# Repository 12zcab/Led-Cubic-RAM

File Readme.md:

# A SOUP-A COOL RAM-based LED CUBE for Retro Computers!
## Images

## Zine Page

## What it does?
It have a normal SRAM pinout for Retro Computer. HOWEVER,ANY DATA YOU STORED INTO IT WILL BE RESULTED AS LIGHT SHINING!!!!
Each RGB LED = 1 Byte from 0 to FF , meaning it have 16 Color Depth for each channel (RGB)
It's works similar to a VRAM with a parallel Dual-DataBus CMOS SRAM.
Really Cool for retro computers as a Screen or a Output or even for Debugging
## Why I made this?
Because I have designed and will design many Z80 and 8086,88 based retro computers and VGA is just too hard for me to design but I don't really like using a Arduino or Serial IC to Debug so I made this RGB Led Cube with 512 Leds to Visualize my RAM usage :D
## How to Assemble it?
As I have not yet built it irl,I can't provide and photo right now...
But Basically it work like this:
1.You need to Order a PCBA service from JLCPCB as this save u a lot of time and much safer as soldering SMT components is not something everybody can handle.

2.You need to Solder IC sockets and PinHeaders

3.Prepare a Hard Copper 0.8mm Diameter Wire and split it into 5 segments each about 30CM

4.solder the copper Wire into the 5V and GND hole on the mainboard PCB

5.Put in esp32 and the RAM and the Oled to test if the mainboard works

6.Start stacking the RGB Led Board and solder the GND and 5V hole of it,remember to align all the DIN DOUT hole on the same side.

7.solder the DIN hole of the bottom RGB LED Board to the Main Board.

8.Solder the Upper DIN hole to the Lower DOUT hole for every single RGB LED Board (YEAH THIS PROJECT IS EXTENDABLE U BASICALLY CAN STACK UNLIMITED RGB BOARDS!!(Yah but the FPS will be lowered actually))

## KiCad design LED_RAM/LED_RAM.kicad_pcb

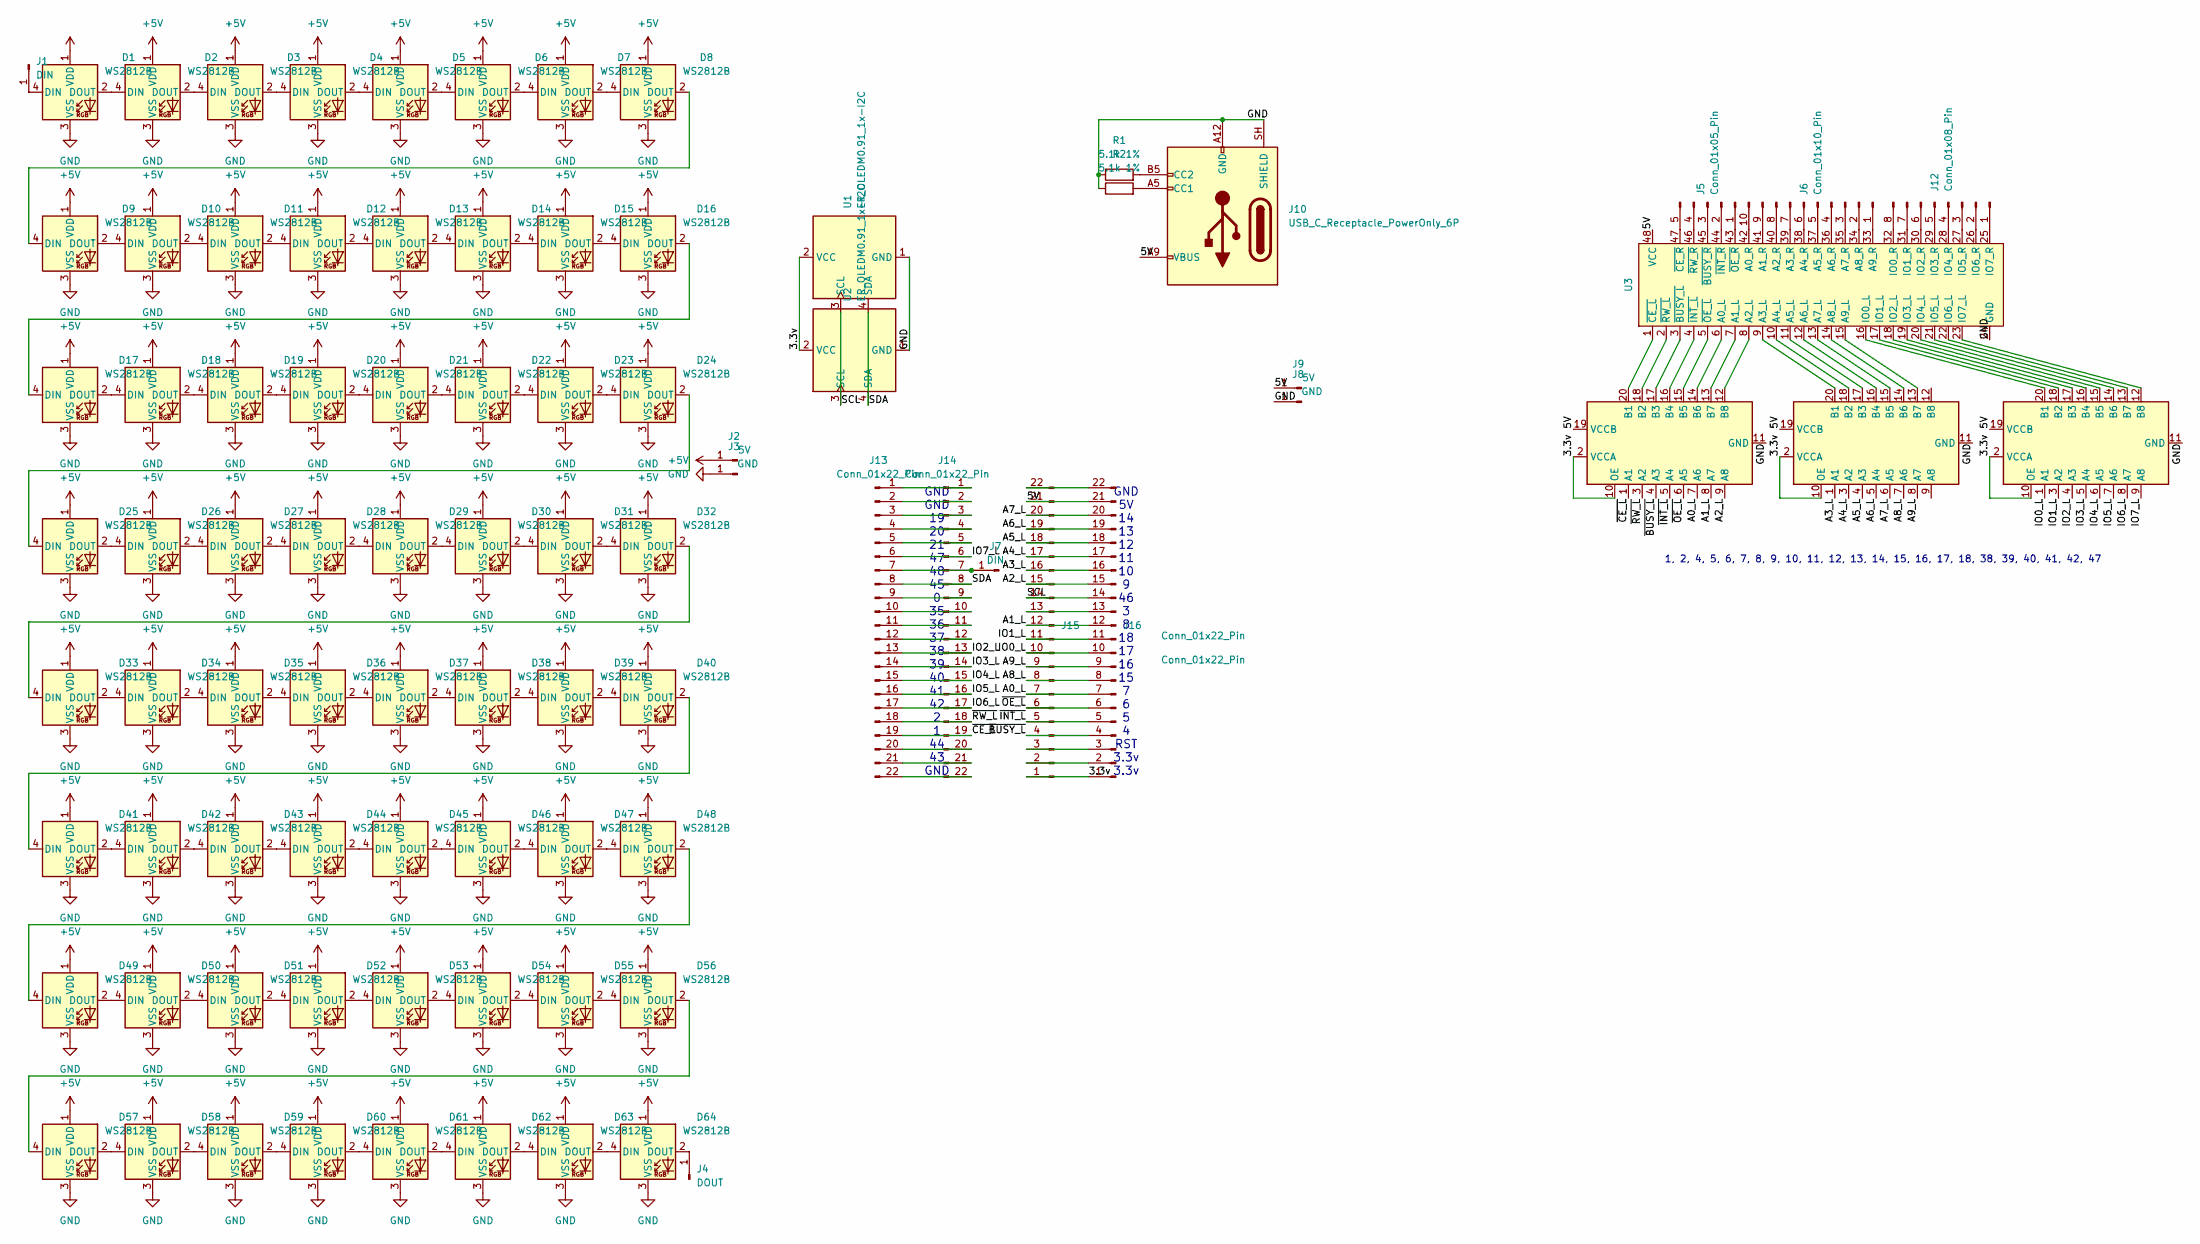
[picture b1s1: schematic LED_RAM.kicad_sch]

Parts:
D1, D2, D3, D4, D5, D6, D7, D8, D9, D10, D11, D12, D13, D14, D15, D16, D17, D18, D19, D20, D21, D22, D23, D24, D25, D26, D27, D28, D29, D30, D31, D32, D33, D34, D35, D36, D37, D38, D39, D40, D41, D42, D43, D44, D45, D46, D47, D48, D49, D50, D51, D52, D53, D54, D55, D56, D57, D58, D59, D60, D61, D62, D63, D64: WS2812B; LED_WS2812B_PLCC4_5.0x5.0mm_P3.2mm
J1, J7: DIN; PinHeader_1x01_P2.54mm_Vertical
J2, J9: 5V; PinHeader_1x01_P2.54mm_Vertical
J3, J8: GND; PinHeader_1x01_P2.54mm_Vertical
J4: DOUT; PinHeader_1x01_P2.54mm_Vertical
J5: Conn_01x05_Pin; PinHeader_1x05_P2.54mm_Vertical
J6: Conn_01x10_Pin; PinHeader_1x10_P2.54mm_Vertical
J10: USB_C_Receptacle_PowerOnly_6P; USB_C_Receptacle_GCT_USB4125-xx-x_6P_TopMnt_Horizontal
J12: Conn_01x08_Pin; PinHeader_1x08_P2.54mm_Vertical
J13, J14, J15, J16: Conn_01x22_Pin; PinHeader_1x22_P2.54mm_Vertical
R1, R2: 5.1k 1%; R_Axial_DIN0207_L6.3mm_D2.5mm_P7.62mm_Horizontal
U1, U2: ER_OLEDM0.91_1x-I2C
U3: DIP-48_W15.24mm
U5, U6, U7: TXS0108EPW; TSSOP-20_4.4x6.5mm_P0.65mm

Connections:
+5V: D1.1 (VDD), D2.1 (VDD), D3.1 (VDD), D4.1 (VDD), D5.1 (VDD), D6.1 (VDD), D7.1 (VDD), D8.1 (VDD), D9.1 (VDD), D10.1 (VDD), D11.1 (VDD), D12.1 (VDD), D13.1 (VDD), D14.1 (VDD), D15.1 (VDD), D16.1 (VDD), D17.1 (VDD), D18.1 (VDD), D19.1 (VDD), D20.1 (VDD), D21.1 (VDD), D22.1 (VDD), D23.1 (VDD), D24.1 (VDD), D25.1 (VDD), D26.1 (VDD), D27.1 (VDD), D28.1 (VDD), D29.1 (VDD), D30.1 (VDD), D31.1 (VDD), D32.1 (VDD), D33.1 (VDD), D34.1 (VDD), D35.1 (VDD), D36.1 (VDD), D37.1 (VDD), D38.1 (VDD), D39.1 (VDD), D40.1 (VDD), D41.1 (VDD), D42.1 (VDD), D43.1 (VDD), D44.1 (VDD), D45.1 (VDD), D46.1 (VDD), D47.1 (VDD), D48.1 (VDD), D49.1 (VDD), D50.1 (VDD), D51.1 (VDD), D52.1 (VDD), D53.1 (VDD), D54.1 (VDD), D55.1 (VDD), D56.1 (VDD), D57.1 (VDD), D58.1 (VDD), D59.1 (VDD), D60.1 (VDD), D61.1 (VDD), D62.1 (VDD), D63.1 (VDD), D64.1 (VDD), J2.1 (Pin_1_1); also elsewhere on the board
/3.3v: J15.1, J16.1, U1.2 (VCC), U2.2 (VCC), U5.2 (VCCA), U5.10 (OE), U6.2 (VCCA), U6.10 (OE), U7.2 (VCCA), U7.10 (OE)
/5V: J9.1 (Pin_1_1), J10.A9 (VBUS), J10.B9 (VBUS), J15.21, J16.21, U3.48 (VCC), U5.19 (VCCB), U6.19 (VCCB), U7.19 (VCCB); also elsewhere on the board
/A0_L: J15.7, J16.7, U5.7 (A6)
/A1_L: J15.12, J16.12, U5.8 (A7)
/A2_L: J15.15, J16.15, U5.9 (A8)
/A3_L: J15.16, J16.16, U6.1 (A1)
/A4_L: J15.17, J16.17, U6.3 (A2)
/A5_L: J15.18, J16.18, U6.4 (A3)
/A6_L: J15.19, J16.19, U6.5 (A4)
/A7_L: J15.20, J16.20, U6.6 (A5)
/A8_L: J15.8, J16.8, U6.7 (A6)
/A9_L: J15.9, J16.9, U6.8 (A7)
/IO0_L: J15.10, J16.10, U7.1 (A1)
/IO1_L: J15.11, J16.11, U7.3 (A2)
/IO2_L: J13.13, J14.13, U7.4 (A3)
/IO3_L: J13.14, J14.14, U7.5 (A4)
/IO4_L: J13.15, J14.15, U7.6 (A5)
/IO5_L: J13.16, J14.16, U7.7 (A6)
/IO6_L: J13.17, J14.17, U7.8 (A7)
/IO7_L: J13.6, J14.6, U7.9 (A8)
/SCL: J15.14, J16.14, U1.3 (SCL), U2.3 (SCL)
/SDA: J13.8, J14.8, U1.4 (SDA), U2.4 (SDA)
/~BUSY_L: J15.4, J16.4, U5.4 (A3)
/~CE_L: J13.19, J14.19, U5.1 (A1)
/~INT_L: J15.5, J16.5, U5.5 (A4)
/~OE_L: J15.6, J16.6, U5.6 (A5)
/~RW_L: J13.18, J14.18, U5.3 (A2)
GND: D1.3 (VSS), D2.3 (VSS), D3.3 (VSS), D4.3 (VSS), D5.3 (VSS), D6.3 (VSS), D7.3 (VSS), D8.3 (VSS), D9.3 (VSS), D10.3 (VSS), D11.3 (VSS), D12.3 (VSS), D13.3 (VSS), D14.3 (VSS), D15.3 (VSS), D16.3 (VSS), D17.3 (VSS), D18.3 (VSS), D19.3 (VSS), D20.3 (VSS), D21.3 (VSS), D22.3 (VSS), D23.3 (VSS), D24.3 (VSS), D25.3 (VSS), D26.3 (VSS), D27.3 (VSS), D28.3 (VSS), D29.3 (VSS), D30.3 (VSS), D31.3 (VSS), D32.3 (VSS), D33.3 (VSS), D34.3 (VSS), D35.3 (VSS), D36.3 (VSS), D37.3 (VSS), D38.3 (VSS), D39.3 (VSS), D40.3 (VSS), D41.3 (VSS), D42.3 (VSS), D43.3 (VSS), D44.3 (VSS), D45.3 (VSS), D46.3 (VSS), D47.3 (VSS), D48.3 (VSS), D49.3 (VSS), D50.3 (VSS), D51.3 (VSS), D52.3 (VSS), D53.3 (VSS), D54.3 (VSS), D55.3 (VSS), D56.3 (VSS), D57.3 (VSS), D58.3 (VSS), D59.3 (VSS), D60.3 (VSS), D61.3 (VSS), D62.3 (VSS), D63.3 (VSS), D64.3 (VSS), J3.1 (Pin_1_1), J8.1 (Pin_1_1), J10.A12 (GND), J10.B12 (GND), J10.SH (SHIELD), R1.1, R2.1, U1.1 (GND), U2.1 (GND), U3.24 (GND), U5.11 (GND), U6.11 (GND), U7.11 (GND); also elsewhere on the board
unnamed: D1.4 (DIN), J1.1 (Pin_1_1)
unnamed: D1.2 (DOUT), D2.4 (DIN)
unnamed: D2.2 (DOUT), D3.4 (DIN)
unnamed: D3.2 (DOUT), D4.4 (DIN)
unnamed: D4.2 (DOUT), D5.4 (DIN)
unnamed: D5.2 (DOUT), D6.4 (DIN)
unnamed: D6.2 (DOUT), D7.4 (DIN)
unnamed: D7.2 (DOUT), D8.4 (DIN)
unnamed: D8.2 (DOUT), D9.4 (DIN)
unnamed: D9.2 (DOUT), D10.4 (DIN)
unnamed: D10.2 (DOUT), D11.4 (DIN)
unnamed: D11.2 (DOUT), D12.4 (DIN)
unnamed: D12.2 (DOUT), D13.4 (DIN)
unnamed: D13.2 (DOUT), D14.4 (DIN)
unnamed: D14.2 (DOUT), D15.4 (DIN)
unnamed: D15.2 (DOUT), D16.4 (DIN)
unnamed: D16.2 (DOUT), D17.4 (DIN)
unnamed: D17.2 (DOUT), D18.4 (DIN)
unnamed: D18.2 (DOUT), D19.4 (DIN)
unnamed: D19.2 (DOUT), D20.4 (DIN)
unnamed: D20.2 (DOUT), D21.4 (DIN)
unnamed: D21.2 (DOUT), D22.4 (DIN)
unnamed: D22.2 (DOUT), D23.4 (DIN)
unnamed: D23.2 (DOUT), D24.4 (DIN)
unnamed: D24.2 (DOUT), D25.4 (DIN)
unnamed: D25.2 (DOUT), D26.4 (DIN)
unnamed: D26.2 (DOUT), D27.4 (DIN)
unnamed: D27.2 (DOUT), D28.4 (DIN)
unnamed: D28.2 (DOUT), D29.4 (DIN)
unnamed: D29.2 (DOUT), D30.4 (DIN)
unnamed: D30.2 (DOUT), D31.4 (DIN)
unnamed: D31.2 (DOUT), D32.4 (DIN)
unnamed: D32.2 (DOUT), D33.4 (DIN)
unnamed: D33.2 (DOUT), D34.4 (DIN)
unnamed: D34.2 (DOUT), D35.4 (DIN)
unnamed: D35.2 (DOUT), D36.4 (DIN)
unnamed: D36.2 (DOUT), D37.4 (DIN)
unnamed: D37.2 (DOUT), D38.4 (DIN)
unnamed: D38.2 (DOUT), D39.4 (DIN)
unnamed: D39.2 (DOUT), D40.4 (DIN)
unnamed: D40.2 (DOUT), D41.4 (DIN)
unnamed: D41.2 (DOUT), D42.4 (DIN)
unnamed: D42.2 (DOUT), D43.4 (DIN)
unnamed: D43.2 (DOUT), D44.4 (DIN)
unnamed: D44.2 (DOUT), D45.4 (DIN)
unnamed: D45.2 (DOUT), D46.4 (DIN)
unnamed: D46.2 (DOUT), D47.4 (DIN)
unnamed: D47.2 (DOUT), D48.4 (DIN)
unnamed: D48.2 (DOUT), D49.4 (DIN)
unnamed: D49.2 (DOUT), D50.4 (DIN)
unnamed: D50.2 (DOUT), D51.4 (DIN)
unnamed: D51.2 (DOUT), D52.4 (DIN)
unnamed: D52.2 (DOUT), D53.4 (DIN)
unnamed: D53.2 (DOUT), D54.4 (DIN)
unnamed: D54.2 (DOUT), D55.4 (DIN)
unnamed: D55.2 (DOUT), D56.4 (DIN)
unnamed: D56.2 (DOUT), D57.4 (DIN)
unnamed: D57.2 (DOUT), D58.4 (DIN)
unnamed: D58.2 (DOUT), D59.4 (DIN)
unnamed: D59.2 (DOUT), D60.4 (DIN)
unnamed: D60.2 (DOUT), D61.4 (DIN)
unnamed: D61.2 (DOUT), D62.4 (DIN)
unnamed: D62.2 (DOUT), D63.4 (DIN)
unnamed: D63.2 (DOUT), D64.4 (DIN)
unnamed: D64.2 (DOUT), J4.1 (Pin_1_1)
unnamed: J5.1, U3.43 (~OE_R)
unnamed: J5.2, U3.44 (~INT_R)
unnamed: J5.3, U3.45 (~BUSY_R)
unnamed: J5.4, U3.46 (~RW_R)
unnamed: J5.5, U3.47 (~CE_R)
unnamed: J6.1, U3.33 (A9_R)
unnamed: J6.2, U3.34 (A8_R)
unnamed: J6.3, U3.35 (A7_R)
unnamed: J6.4, U3.36 (A6_R)
unnamed: J6.5, U3.37 (A5_R)
unnamed: J6.6, U3.38 (A4_R)
unnamed: J6.7, U3.39 (A3_R)
unnamed: J6.8, U3.40 (A2_R)
unnamed: J6.9, U3.41 (A1_R)
unnamed: J6.10, U3.42 (A0_R)
unnamed: J10.A5 (CC1), R2.2
unnamed: J10.B5 (CC2), R1.2
unnamed: J12.1, U3.25 (IO7_R)
unnamed: J12.2, U3.26 (IO6_R)
unnamed: J12.3, U3.27 (IO5_R)
unnamed: J12.4, U3.28 (IO4_R)
unnamed: J12.5, U3.29 (IO3_R)
unnamed: J12.6, U3.30 (IO2_R)
unnamed: J12.7, U3.31 (IO1_R)
unnamed: J12.8, U3.32 (IO0_R)
unnamed: J13.1, J14.1
unnamed: J13.2, J14.2
unnamed: J13.3, J14.3
unnamed: J13.4, J14.4
unnamed: J13.5, J14.5
unnamed: J7.1 (Pin_1_1), J13.7, J14.7
unnamed: J13.9, J14.9
unnamed: J13.10, J14.10
unnamed: J13.11, J14.11
unnamed: J13.12, J14.12
unnamed: J13.20, J14.20
unnamed: J13.21, J14.21
unnamed: J13.22, J14.22
unnamed: J15.2, J16.2
unnamed: J15.3, J16.3
unnamed: J15.13, J16.13
unnamed: J15.22, J16.22
unnamed: U3.6 (A0_L), U5.14 (B6)
unnamed: U3.7 (A1_L), U5.13 (B7)
unnamed: U3.8 (A2_L), U5.12 (B8)
unnamed: U3.9 (A3_L), U6.20 (B1)
unnamed: U3.10 (A4_L), U6.18 (B2)
unnamed: U3.11 (A5_L), U6.17 (B3)
unnamed: U3.12 (A6_L), U6.16 (B4)
unnamed: U3.13 (A7_L), U6.15 (B5)
unnamed: U3.14 (A8_L), U6.14 (B6)
unnamed: U3.15 (A9_L), U6.13 (B7)
unnamed: U3.16 (IO0_L), U7.20 (B1)
unnamed: U3.17 (IO1_L), U7.18 (B2)
unnamed: U3.18 (IO2_L), U7.17 (B3)
unnamed: U3.19 (IO3_L), U7.16 (B4)
unnamed: U3.20 (IO4_L), U7.15 (B5)
unnamed: U3.21 (IO5_L), U7.14 (B6)
unnamed: U3.22 (IO6_L), U7.13 (B7)
unnamed: U3.23 (IO7_L), U7.12 (B8)
unnamed: U3.3 (~BUSY_L), U5.17 (B3)
unnamed: U3.1 (~CE_L), U5.20 (B1)
unnamed: U3.4 (~INT_L), U5.16 (B4)
unnamed: U3.5 (~OE_L), U5.15 (B5)
unnamed: U3.2 (~RW_L), U5.18 (B2)

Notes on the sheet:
GND GND 19 20 21 47 48 45 0 35 36 37 38 39 40 41 42 2 1 44 43 GND
1, 2, 4, 5, 6, 7, 8, 9, 10, 11, 12, 13, 14, 15, 16, 17, 18, 38, 39, 40, 41, 42, 47
GND 5V 14 13 12 11 10 9 46 3 8 18 17 16 15 7 6 5 4 RST 3.3v 3.3v

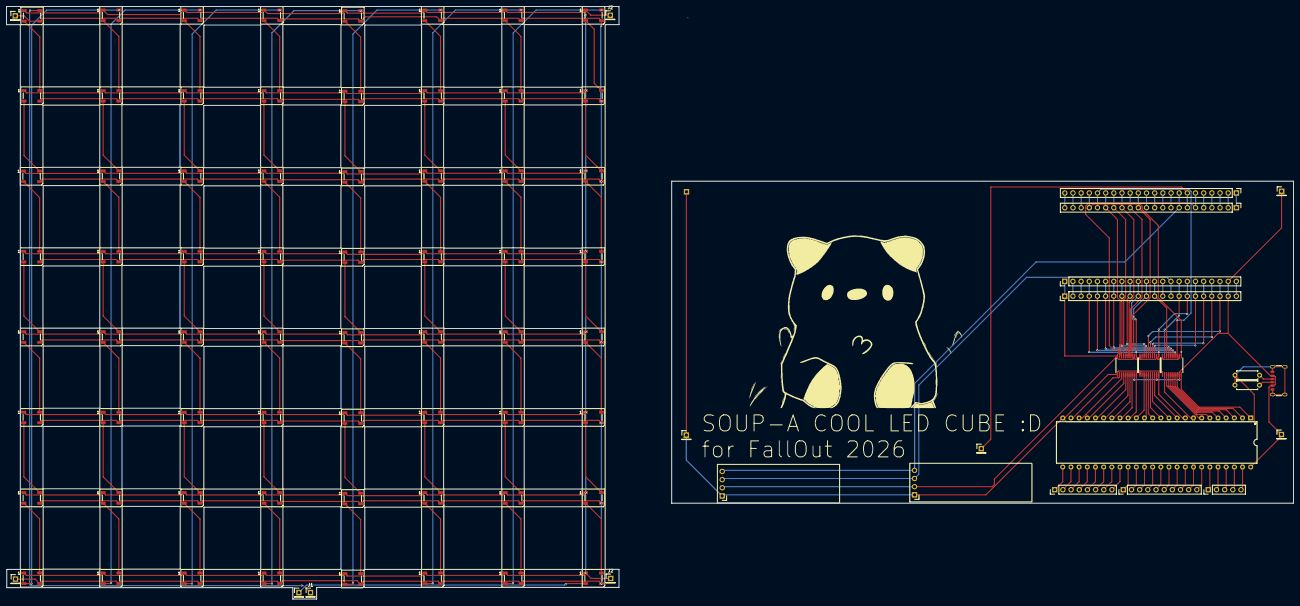
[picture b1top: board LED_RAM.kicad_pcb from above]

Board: 2 copper layers, 400.1 x 184.2 mm, 90 parts (0 on the bottom side), 159 nets.

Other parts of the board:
J2#2, J9#2: 5V; PinHeader_1x01_P2.54mm_Vertical
J3#2: GND; PinHeader_1x01_P2.54mm_Vertical

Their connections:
+5V: J2#2.1 (Pin_1_1); also elsewhere on the board
/5V: J9#2.1 (Pin_1_1); also elsewhere on the board
GND: J3#2.1 (Pin_1_1); also elsewhere on the board

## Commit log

2026-06-15 Enhance Arduino program with memory reading and pin setup
    Added memory read functionality and updated pin configurations.
